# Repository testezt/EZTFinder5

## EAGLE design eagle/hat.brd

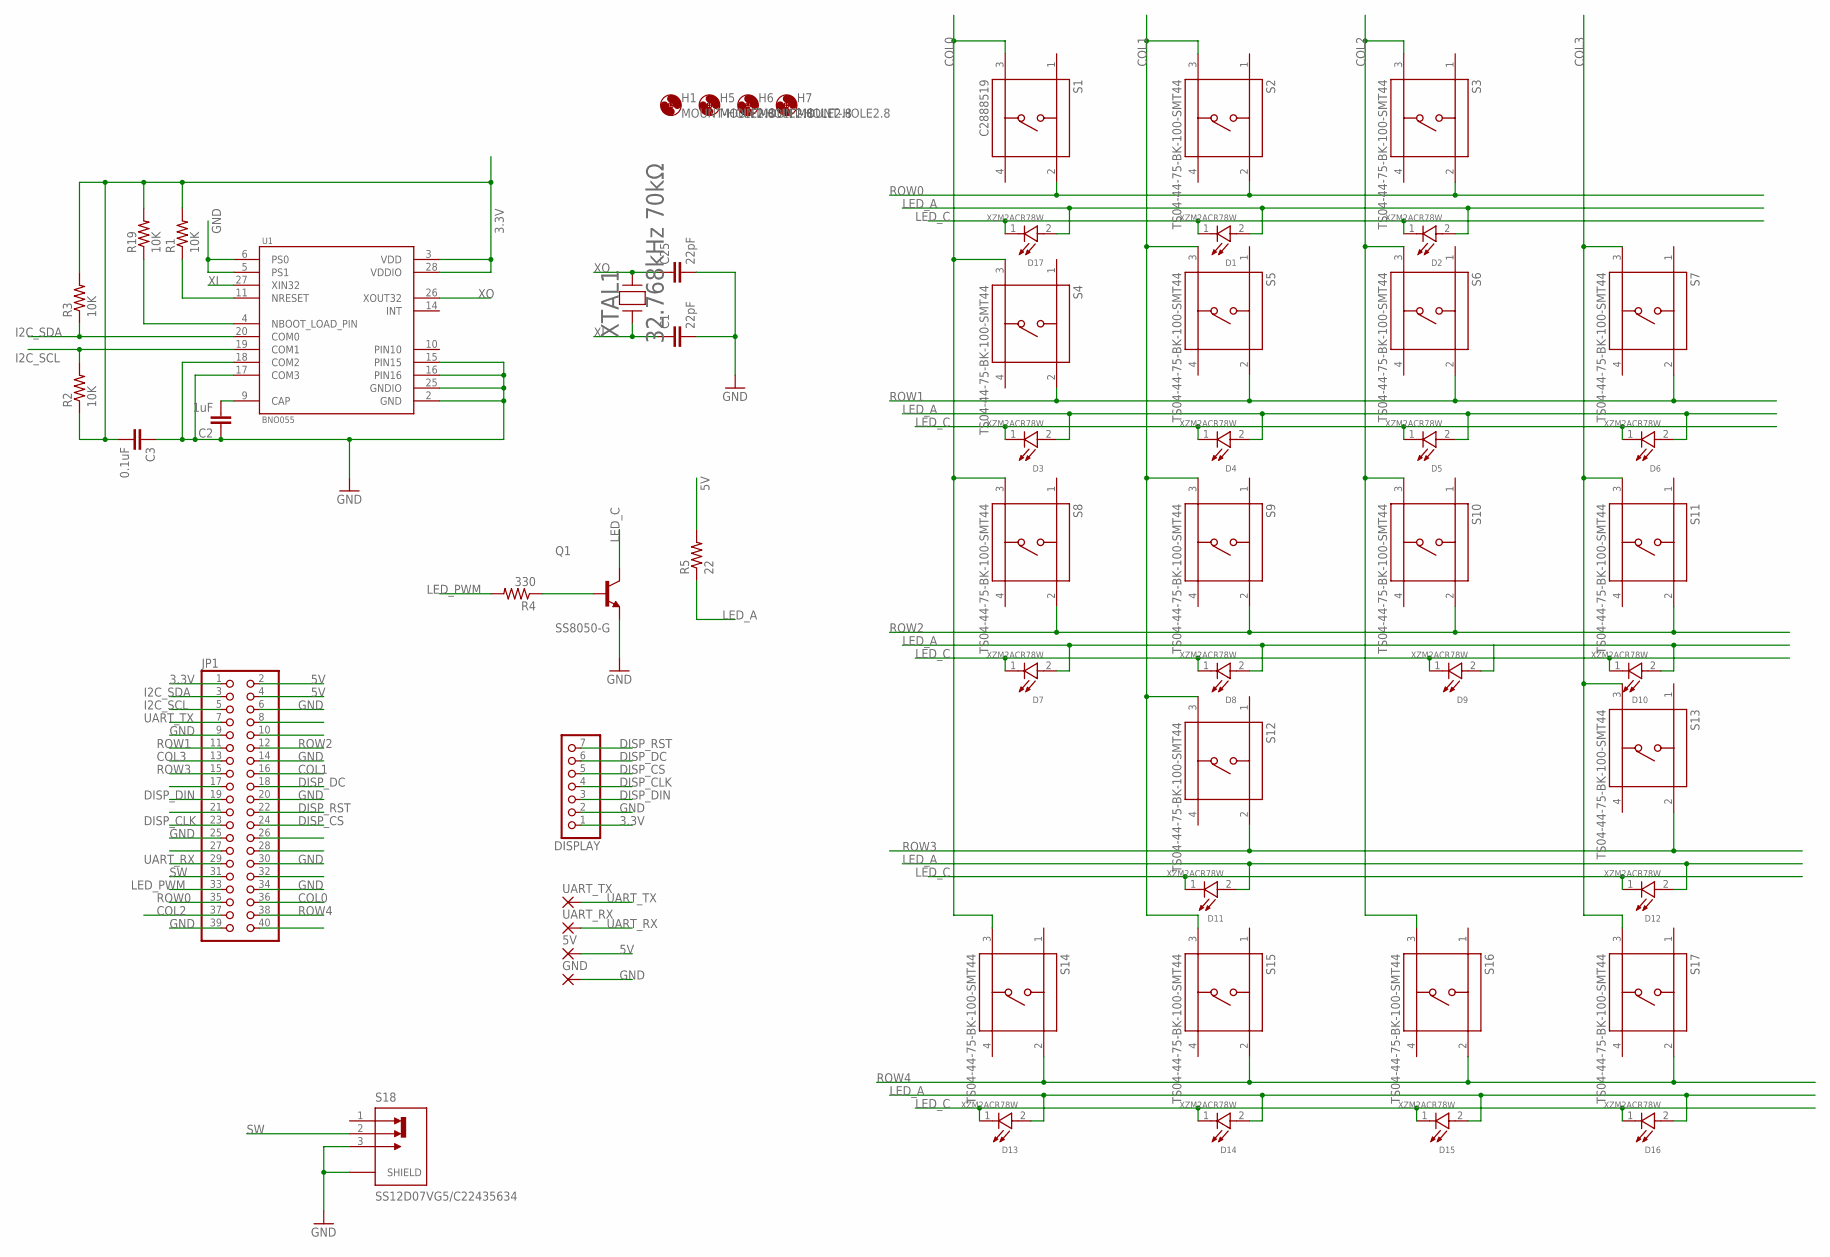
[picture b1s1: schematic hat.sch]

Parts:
5V: SMD2; SMD1,27-2,54
C1, C25: 22pF; CAP_0603
C2: 1uF; CAP_0603
C3: 0.1uF; CAP_0603
D1, D2, D3, D4, D5, D6, D7, D8, D9, D10, D11, D12, D13, D14, D15, D16, D17: XZM2ACR78W; LED_XZM2ACR78W
DISPLAY: PINHD-1X7; 1X07
GND: SMD2; SMD1,27-2,54
H1, H5, H6, H7: MOUNT-HOLE2.8; 2,8
JP1: PINHD-2X20; 2X20
Q1: SS8050-G; TRANS_SS8050-G
R1, R2, R3, R19: 10K; RES_0603
R4: 330; RES_0603
R5: 22; RES_0603
S1: C2888519; SW_TS04-44
S2, S3, S4, S5, S6, S7, S8, S9, S10, S11, S12, S13, S14, S15, S16, S17: TS04-44-75-BK-100-SMT44; SW_TS04-44
S18: SS12D07VG5/C22435634; SW_SS12D07VG4
U1: BNO055; LGA28R50P4X10_380X520X100
UART_RX: SMD2; SMD1,27-2,54
UART_TX: SMD2; SMD1,27-2,54
XTAL1: 32.768kHz 70kΩ; XTAL_FC-135_EPS

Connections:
3.3V: C3.2, DISPLAY.1, JP1.1, R1.2, R2.1, R3.2, R19.2, U1.3 (VDD), U1.28 (VDDIO)
5V: 5V.1, JP1.2, JP1.4, R5.2
COL0: JP1.36, S1.3 (2), S4.3 (2), S8.3 (2), S14.3 (2)
COL1: JP1.16, S2.3 (2), S5.3 (2), S9.3 (2), S12.3 (2), S15.3 (2)
COL2: JP1.37, S3.3 (2), S6.3 (2), S10.3 (2), S16.3 (2)
COL3: JP1.13, S7.3 (2), S11.3 (2), S13.3 (2), S17.3 (2)
DISP_CLK: DISPLAY.4, JP1.23
DISP_CS: DISPLAY.5, JP1.24
DISP_DC: DISPLAY.6, JP1.18
DISP_DIN: DISPLAY.3, JP1.19
DISP_RST: DISPLAY.7, JP1.22
GND: C1.2, C2.1, C3.1, C25.2, DISPLAY.2, GND.1, JP1.6, JP1.9, JP1.14, JP1.20, JP1.25, JP1.30, JP1.34, JP1.39, Q1.2 (E), S18.3, S18.S1 (SHIELD), S18.S2 (SHIELD), U1.2 (GND), U1.5 (PS1), U1.6 (PS0), U1.15 (PIN15), U1.16 (PIN16), U1.17 (COM3), U1.18 (COM2), U1.25 (GNDIO)
I2C_SCL: JP1.5, R2.2, U1.19 (COM1)
I2C_SDA: JP1.3, R3.1, U1.20 (COM0)
LED_A: D1.2 (A), D2.2 (A), D3.2 (A), D4.2 (A), D5.2 (A), D6.2 (A), D7.2 (A), D8.2 (A), D9.2 (A), D10.2 (A), D11.2 (A), D12.2 (A), D13.2 (A), D14.2 (A), D15.2 (A), D16.2 (A), D17.2 (A), R5.1
LED_C: D1.1 (C), D2.1 (C), D3.1 (C), D4.1 (C), D5.1 (C), D6.1 (C), D7.1 (C), D8.1 (C), D9.1 (C), D10.1 (C), D11.1 (C), D12.1 (C), D13.1 (C), D14.1 (C), D15.1 (C), D16.1 (C), D17.1 (C), Q1.3 (C)
LED_PWM: JP1.33, R4.2
unnamed: R1.1, U1.11 (NRESET)
unnamed: R19.1, U1.4 (NBOOT_LOAD_PIN)
unnamed: C2.2, U1.9 (CAP)
unnamed: Q1.1 (B), R4.1
PIN10: U1.10 (PIN10)
ROW0: JP1.35, S1.2 (3), S2.2 (3), S3.2 (3)
ROW1: JP1.11, S4.2 (3), S5.2 (3), S6.2 (3), S7.2 (3)
ROW2: JP1.12, S8.2 (3), S9.2 (3), S10.2 (3), S11.2 (3)
ROW3: JP1.15, S12.2 (3), S13.2 (3)
ROW4: JP1.38, S14.2 (3), S15.2 (3), S16.2 (3), S17.2 (3)
SW: JP1.31, S18.2
UART_RX: JP1.29, UART_RX.1
UART_TX: JP1.7, UART_TX.1
XI: C1.1, U1.27 (XIN32), XTAL1.1
XO: C25.1, U1.26 (XOUT32), XTAL1.2

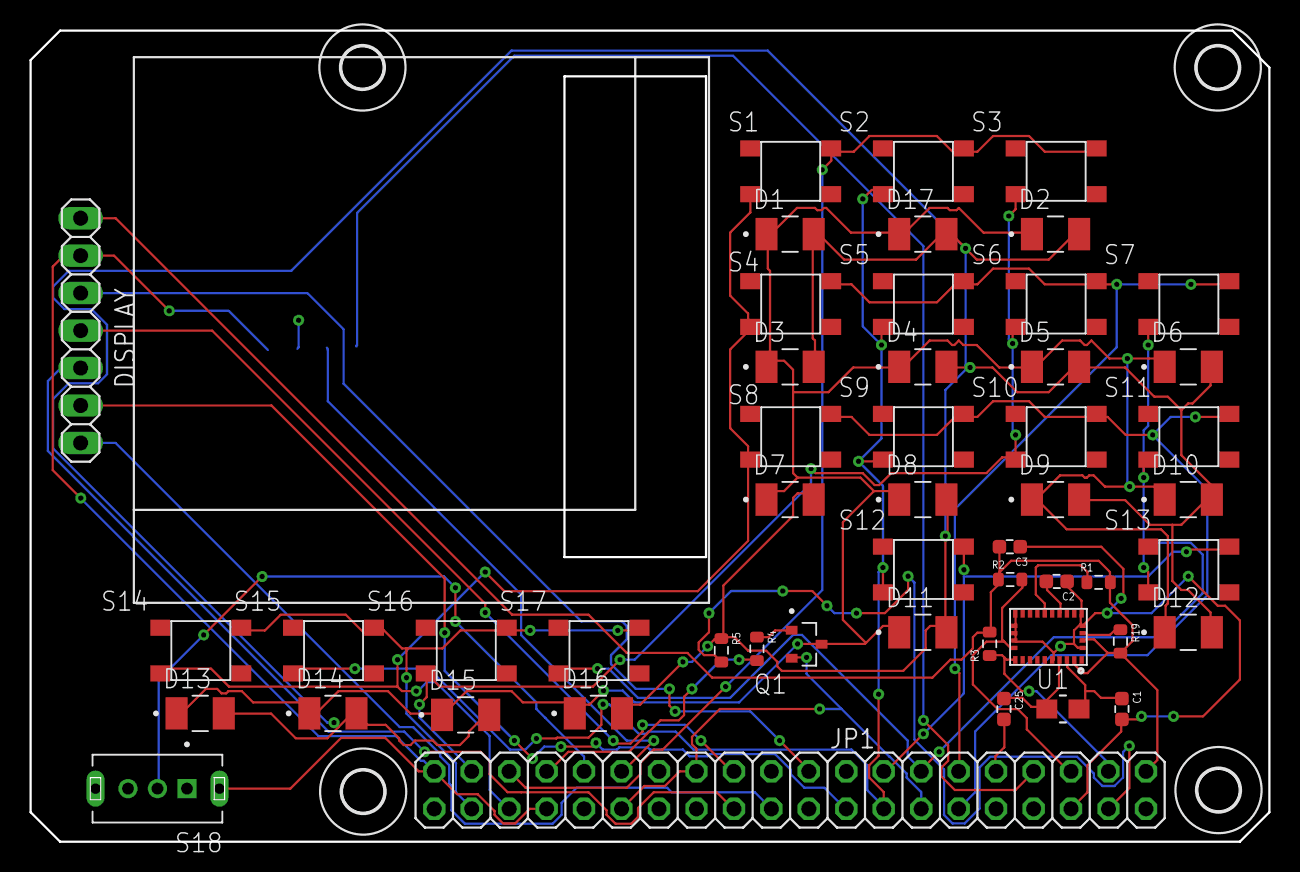
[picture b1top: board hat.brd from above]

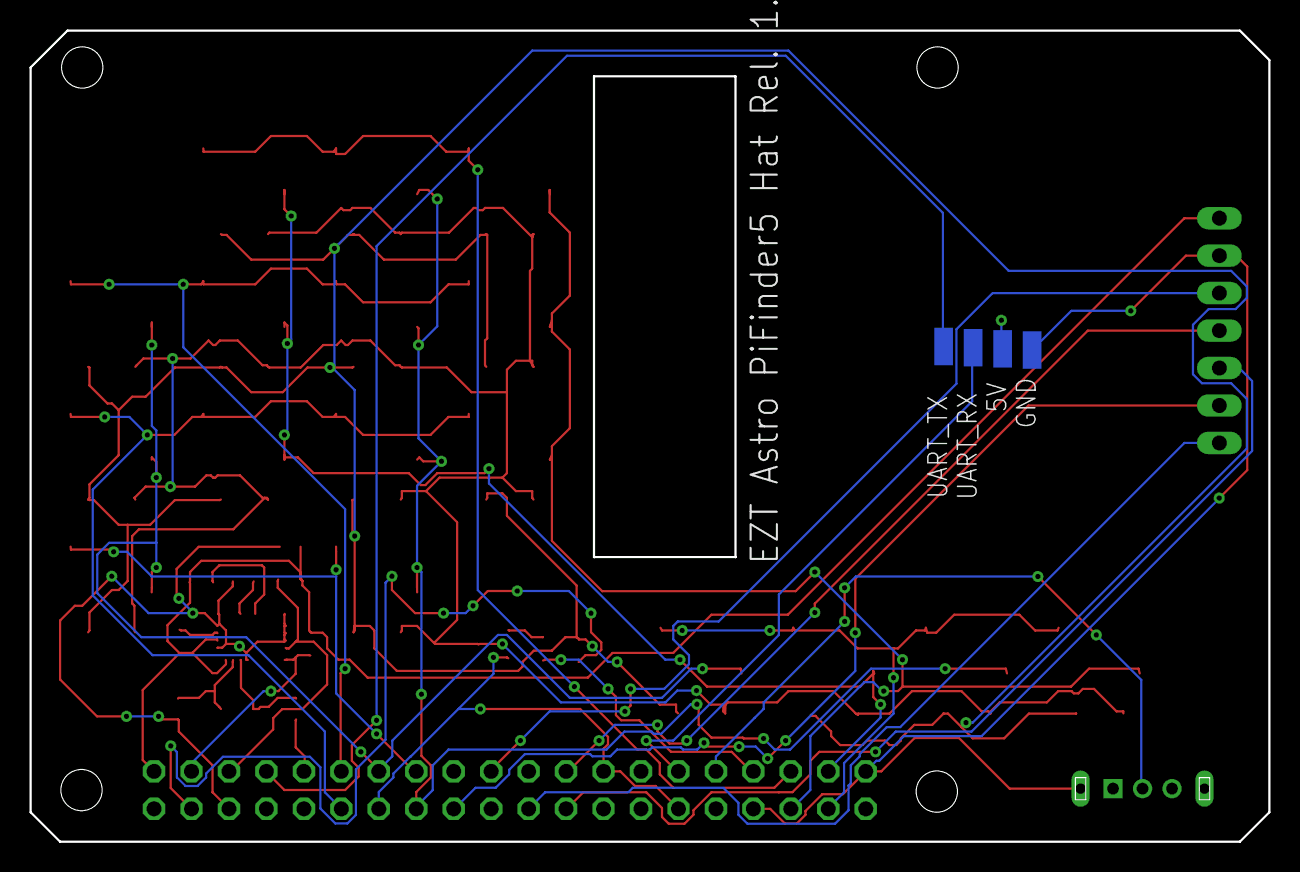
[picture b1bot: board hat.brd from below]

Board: 4 copper layers, 84.0 x 55.0 mm, 58 parts (4 on the bottom side), 31 nets.

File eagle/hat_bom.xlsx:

Comment | Designator | Footprint
22pF | C1 | C0603C100C5GACTU | C1648
1uF | C2 | C0603C100C5GACTU | C15849
22pF | C25 | C0603C100C5GACTU | C1648
0.1uF | C3 | C0603C100C5GACTU | C14663
APBD3224LSYKCGKC | D1 | APBD3224LSYKCGKC | C125112
APBD3224LSYKCGKC | D2 | APBD3224LSYKCGKC | C125112
APBD3224LSYKCGKC | D3 | APBD3224LSYKCGKC | C125112
APBD3224LSYKCGKC | D4 | APBD3224LSYKCGKC | C125112
APBD3224LSYKCGKC | D5 | APBD3224LSYKCGKC | C125112
APBD3224LSYKCGKC | D6 | APBD3224LSYKCGKC | C125112
APBD3224LSYKCGKC | D7 | APBD3224LSYKCGKC | C125112
APBD3224LSYKCGKC | D8 | APBD3224LSYKCGKC | C125112
APBD3224LSYKCGKC | D9 | APBD3224LSYKCGKC | C125112
APBD3224LSYKCGKC | D10 | APBD3224LSYKCGKC | C125112
APBD3224LSYKCGKC | D11 | APBD3224LSYKCGKC | C125112
APBD3224LSYKCGKC | D12 | APBD3224LSYKCGKC | C125112
APBD3224LSYKCGKC | D13 | APBD3224LSYKCGKC | C125112
APBD3224LSYKCGKC | D14 | APBD3224LSYKCGKC | C125112
APBD3224LSYKCGKC | D15 | APBD3224LSYKCGKC | C125112
APBD3224LSYKCGKC | D16 | APBD3224LSYKCGKC | C125112
APBD3224LSYKCGKC | D17 | APBD3224LSYKCGKC | C125112
SS8050-G | Q1 | SS8050-G | C2150
10K | R1 | RC0603JR-070RL | C25804
10K | R2 | RC0603JR-070RL | C25804
10K | R3 | RC0603JR-070RL | C25804
330 | R4 | RC0603JR-070RL | C23138
22 | R5 | RC0603JR-070RL | C103419
10K | R19 | RC0603JR-070RL | C25804
C2888519 | S1 | TS04-44-75-BK-100-SMT44 | C2888519
TS04-44-75-BK-100-SMT44 | S2 | TS04-44-75-BK-100-SMT44 | C2888519
TS04-44-75-BK-100-SMT44 | S3 | TS04-44-75-BK-100-SMT44 | C2888519
TS04-44-75-BK-100-SMT44 | S4 | TS04-44-75-BK-100-SMT44 | C2888519
TS04-44-75-BK-100-SMT44 | S5 | TS04-44-75-BK-100-SMT44 | C2888519
TS04-44-75-BK-100-SMT44 | S6 | TS04-44-75-BK-100-SMT44 | C2888519
TS04-44-75-BK-100-SMT44 | S7 | TS04-44-75-BK-100-SMT44 | C2888519
TS04-44-75-BK-100-SMT44 | S8 | TS04-44-75-BK-100-SMT44 | C2888519
TS04-44-75-BK-100-SMT44 | S9 | TS04-44-75-BK-100-SMT44 | C2888519
TS04-44-75-BK-100-SMT44 | S10 | TS04-44-75-BK-100-SMT44 | C2888519
TS04-44-75-BK-100-SMT44 | S11 | TS04-44-75-BK-100-SMT44 | C2888519
TS04-44-75-BK-100-SMT44 | S12 | TS04-44-75-BK-100-SMT44 | C2888519
TS04-44-75-BK-100-SMT44 | S13 | TS04-44-75-BK-100-SMT44 | C2888519
TS04-44-75-BK-100-SMT44 | S14 | TS04-44-75-BK-100-SMT44 | C2888519
TS04-44-75-BK-100-SMT44 | S15 | TS04-44-75-BK-100-SMT44 | C2888519
TS04-44-75-BK-100-SMT44 | S16 | TS04-44-75-BK-100-SMT44 | C2888519
TS04-44-75-BK-100-SMT44 | S17 | TS04-44-75-BK-100-SMT44 | C2888519
SS12D07VG5/C22435634 | S18 | SS12D07VG4 | C22435634
BNO055 | U1 | BNO055 | C93216
32.768kHz 70kΩ | XTAL1 | Q13FC1350000400 | C32346

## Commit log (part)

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2026-02-22 Initial project upload
2026-02-22 Add Korean translation
2026-02-22 Update post-update script source path
2026-02-23 Update migration sources and requirements for EZTFinder5
2026-02-28 New welcome image
2026-02-28 welcome image
2026-02-28 EZTFinder
2026-02-28 Finder Type
2026-03-15 Revise mount control
2026-03-15 locale
2026-03-15 font
2026-03-15 version change
2026-03-16 path
2026-03-16 overwrite update
2026-03-16 update version
2026-03-17 splash image
2026-03-17 welcome
2026-03-18 Max refine tries
2026-03-19 Update korean
2026-03-19 Increment version to 2.3.5
2026-03-19 Update refine slew delay and max number of tries.
2026-03-19 version
2026-03-20 Korean
2026-03-22 update script
2026-04-27 remove cedar detect server
2026-05-02 Remove cedar_detect
2026-05-02 Remove test files
2026-05-05 Add ZWO
2026-05-20 Create new folder for EAGLE
2026-05-20 Faceplate
2026-05-20 Create Fusion
